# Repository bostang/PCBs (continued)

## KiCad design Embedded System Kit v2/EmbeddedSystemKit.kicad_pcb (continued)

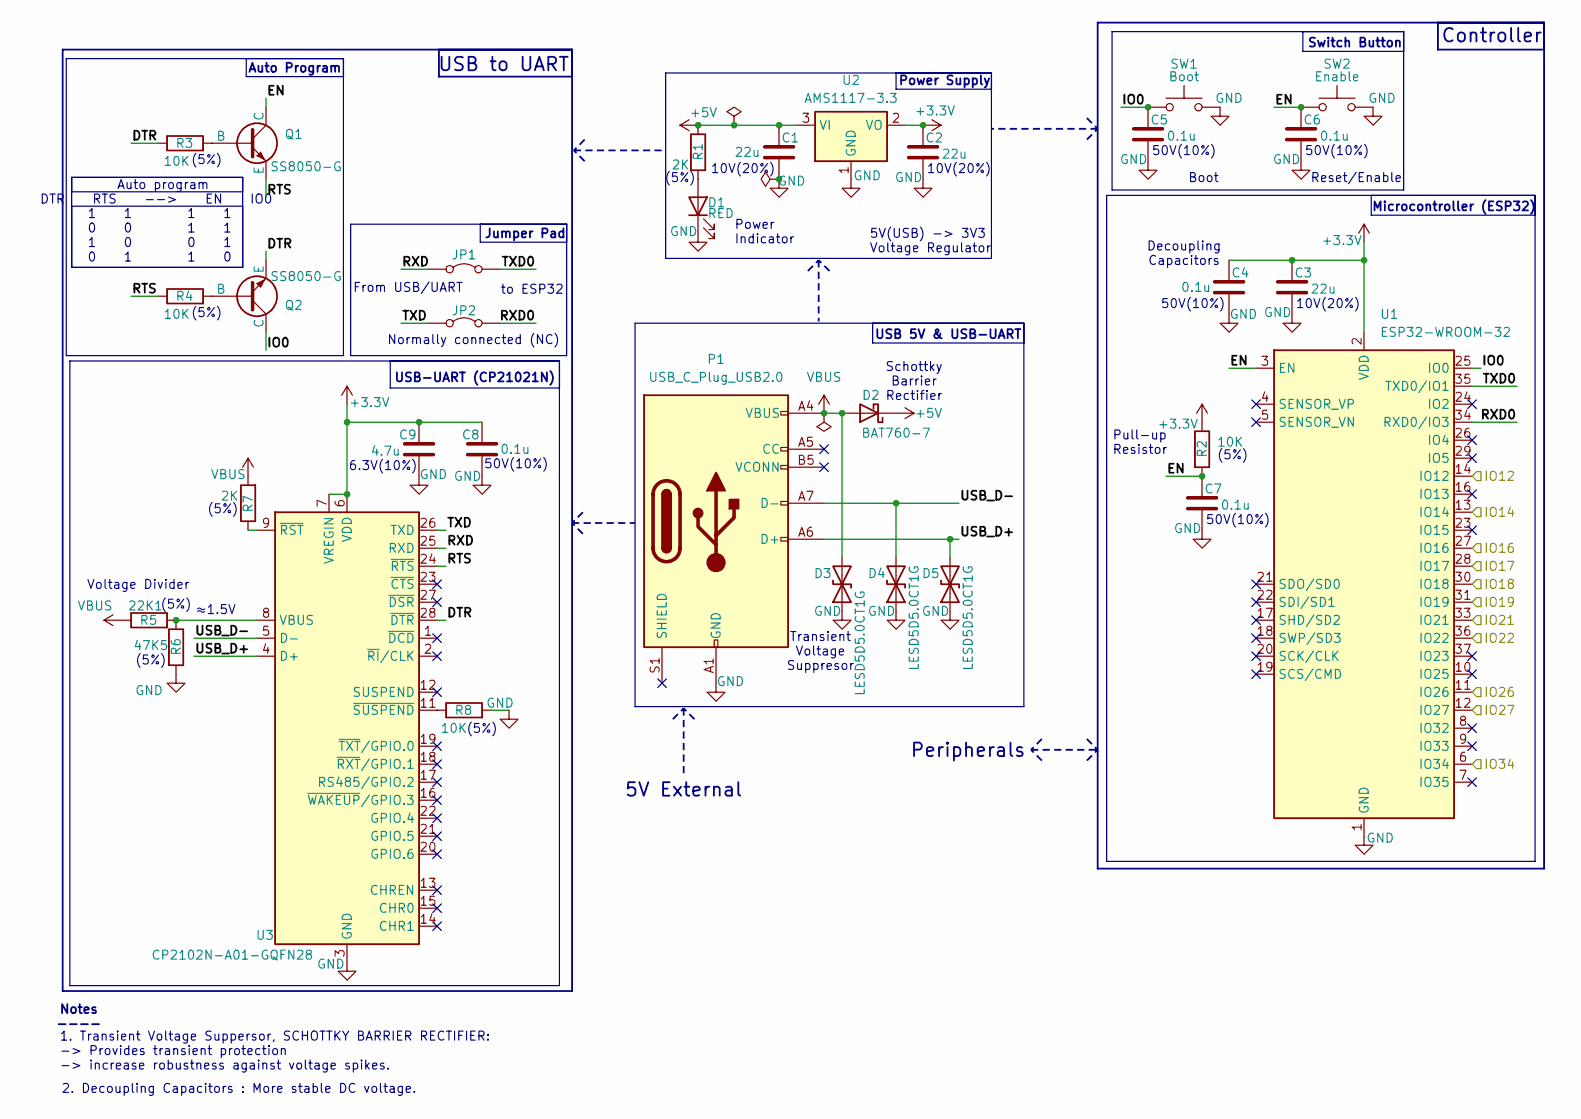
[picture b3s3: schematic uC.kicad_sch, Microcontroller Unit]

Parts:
C1, C2, C3: 22u; C_0805_2012Metric
C4, C5, C6, C7: 0.1u; C_0805_2012Metric
C8: 0.1u; C_0402_1005Metric
C9: 4.7u; C_0402_1005Metric
D1: RED; LED_0805_2012Metric
D2: BAT760-7; D_SOD-323
D3, D4, D5: LESD5D5.0CT1G; D_SOD-523
JP1, JP2: Jumper_2_Bridged; SolderJumper-2_P1.3mm_Bridged_RoundedPad1.0x1.5mm
P1: USB_C_Plug_USB2.0; USB_C_Receptacle_GCT_USB4105-xx-A_16P_TopMnt_Horizontal
Q1, Q2: SS8050-G; SOT-23
R1: 2K; R_0805_2012Metric
R2: 10K; R_0805_2012Metric
R3, R4, R8: 10K; R_0402_1005Metric
R5: 22K1; R_0402_1005Metric
R6: 47K5; R_0402_1005Metric
R7: 2K; R_0402_1005Metric
SW1: Boot; SW_SPST_B3U-1000P
SW2: Enable; SW_SPST_B3U-1000P
U1: ESP32-WROOM-32
U2: AMS1117-3.3; SOT-223-3_TabPin2
U3: CP2102N-A01-GQFN28; QFN-28-1EP_5x5mm_P0.5mm_EP3.35x3.35mm

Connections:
+3.3V: C2.1, C3.1, C4.1, C8.1, C9.1, R2.1, U1.2 (VDD), U2.2 (VO), U3.6 (VDD), U3.7 (VREGIN); also elsewhere on the board
+5V: C1.1, D2.1 (K), R1.1, U2.3 (VI); also elsewhere on the board
/LCD_SCL: U1.36 (IO22); also elsewhere on the board
/LCD_SDA: U1.33 (IO21); also elsewhere on the board
/LED1: U1.14 (IO12); also elsewhere on the board
/LED2: U1.13 (IO14); also elsewhere on the board
/LED3: U1.11 (IO26); also elsewhere on the board
/LED4: U1.12 (IO27); also elsewhere on the board
/PB1: U1.27 (IO16); also elsewhere on the board
/PB2: U1.28 (IO17); also elsewhere on the board
/PB3: U1.30 (IO18); also elsewhere on the board
/PB4: U1.31 (IO19); also elsewhere on the board
/POT: U1.6 (IO34); also elsewhere on the board
/uC/DTR: Q2.3 (E), R3.1, U3.28 (~DTR)
/uC/EN: C6.1, C7.1, Q1.1 (C), R2.2, SW2.1, U1.3 (EN)
/uC/IO0: C5.1, Q2.1 (C), SW1.1, U1.25 (IO0)
/uC/RTS: Q1.3 (E), R4.1, U3.24 (~RTS)
/uC/RXD: JP1.1 (A), U3.25 (RXD)
/uC/RXD0: JP2.2 (B), U1.34 (RXD0/IO3)
/uC/TXD: JP2.1 (A), U3.26 (TXD)
/uC/TXD0: JP1.2 (B), U1.35 (TXD0/IO1)
/uC/USB_D+: D5.2 (A2), P1.A6 (D+), U3.4 (D+)
/uC/USB_D-: D4.2 (A2), P1.A7 (D-), U3.5 (D-)
GND: C1.2, C2.2, C3.2, C4.2, C5.2, C6.2, C7.2, C8.2, C9.2, D1.1 (K), D3.1 (A1), D4.1 (A1), D5.1 (A1), P1.A1 (GND), P1.A12 (GND), P1.B1 (GND), P1.B12 (GND), R6.2, R8.2, SW1.2, SW2.2, U1.1 (GND), U1.15 (GND), U1.38 (GND), U1.39 (GND), U2.1 (GND), U3.3 (GND), U3.29 (GND); also elsewhere on the board
unnamed: D1.2 (A), R1.2
unnamed: Q1.2 (B), R3.2
unnamed: Q2.2 (B), R4.2
unnamed: R5.2, R6.1, U3.8 (VBUS)
unnamed: R7.1, U3.9 (~RST)
unnamed: R8.1, U3.11 (~SUSPEND)
VBUS: D2.2 (A), D3.2 (A2), P1.A4 (VBUS), P1.A9 (VBUS), P1.B4 (VBUS), P1.B9 (VBUS), R5.1, R7.2

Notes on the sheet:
Auto program DTR RTS --> EN IO0 1 1 1 1 0 0 1 1 1 0 0 1 0 1 1 0
Normally connected (NC)
Transient Voltage Suppresor
Auto Program
(5%)
10V(20%)
50V(10%)
Voltage Divider
Microcontroller (ESP32)
Pull-up Resistor
5V(USB) -> 3V3 Voltage Regulator
Power Indicator
From USB/UART
Schottky Barrier Rectifier
to ESP32
6.3V(10%)
Power Supply
Boot
5V External
Decoupling Capacitors
Peripherals
USB-UART (CP21021N)
Notes ----
Jumper Pad
≈1.5V
2. Decoupling Capacitors : More stable DC voltage.
Switch Button
Controller
1. Transient Voltage Suppersor, SCHOTTKY BARRIER RECTIFIER: -> Provides transient protection -> increase robustness against voltage spikes.
USB 5V & USB-UART
USB to UART
Reset/Enable

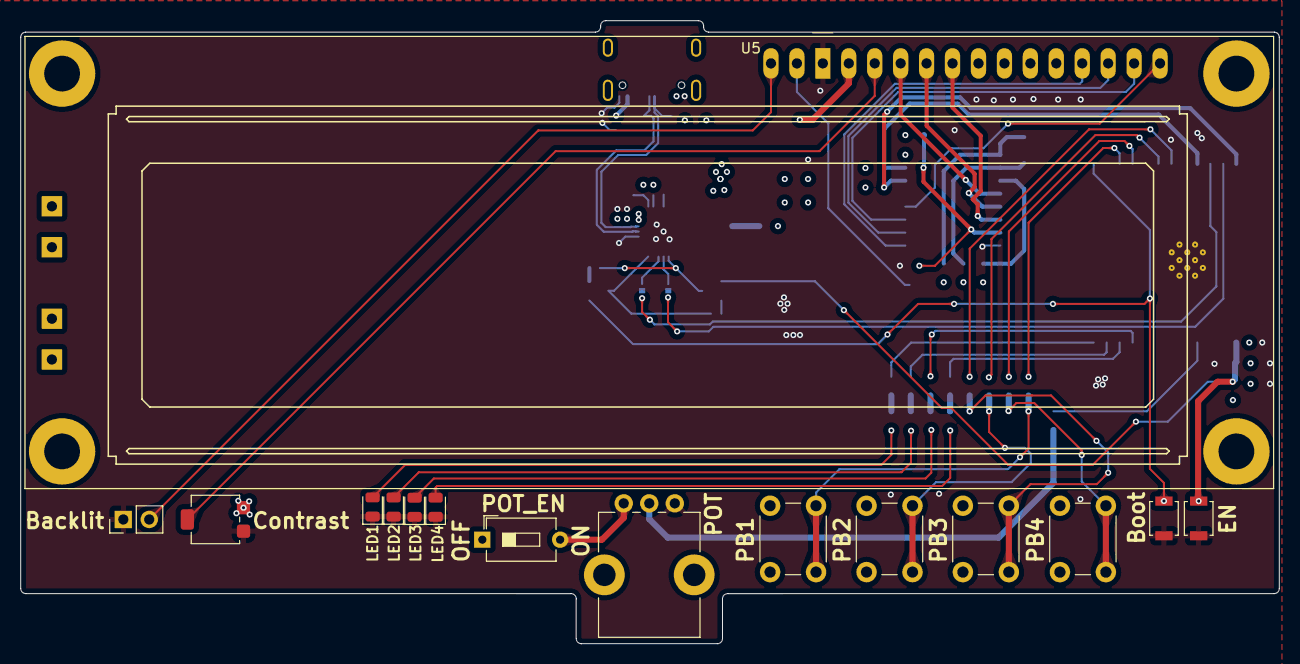
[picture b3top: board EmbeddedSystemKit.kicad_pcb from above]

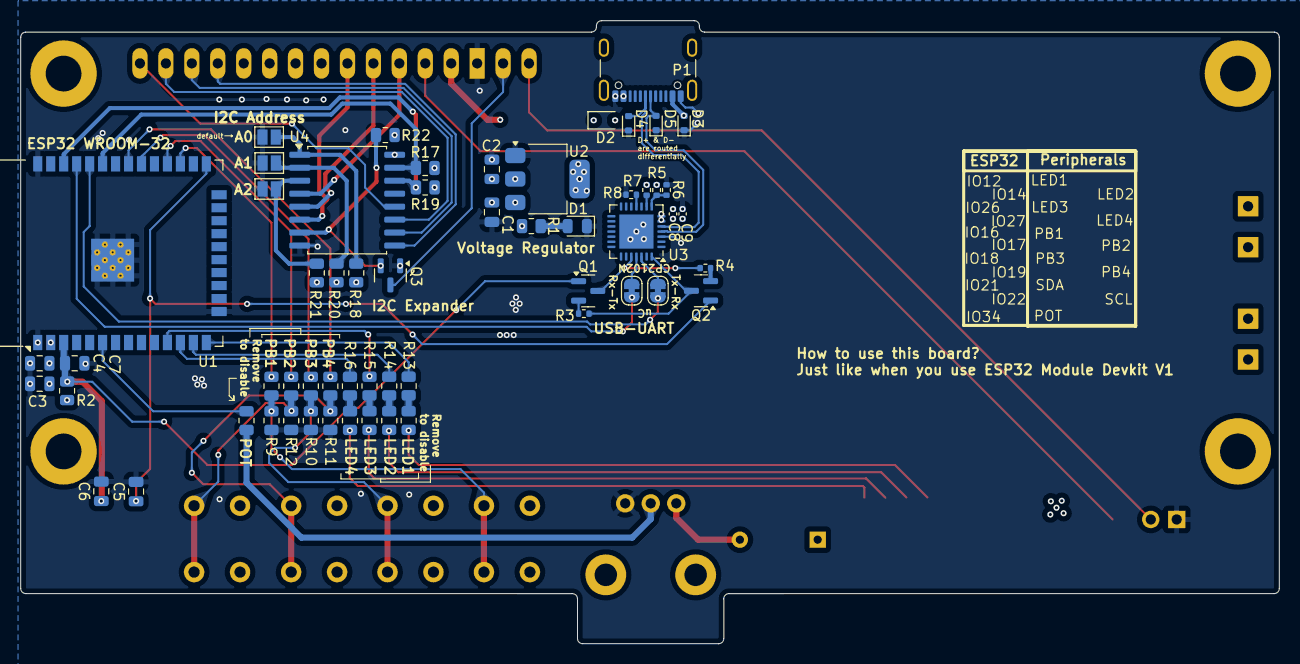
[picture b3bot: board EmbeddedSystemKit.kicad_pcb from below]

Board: 4 copper layers, 123.3 x 61.0 mm, 73 parts (58 on the bottom side), 59 nets.

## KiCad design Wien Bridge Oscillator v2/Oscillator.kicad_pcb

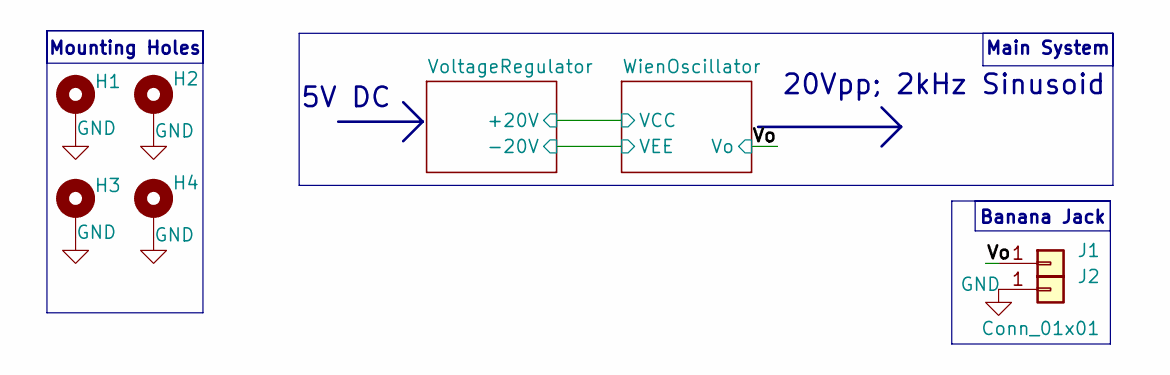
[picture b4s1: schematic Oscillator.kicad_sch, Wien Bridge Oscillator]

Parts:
H1, H2, H3, H4: MountingHole_Pad; MountingHole_2.2mm_M2_Pad_Via
J1, J2: Conn_01x01; TestPoint_Pad_4.0x4.0mm

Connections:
/Vo: J1.1; also elsewhere on the board
GND: H1.1, H2.1, H3.1, H4.1, J2.1; also elsewhere on the board

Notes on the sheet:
20Vpp; 2kHz Sinusoid
5V DC
Mounting Holes
Banana Jack
Main System

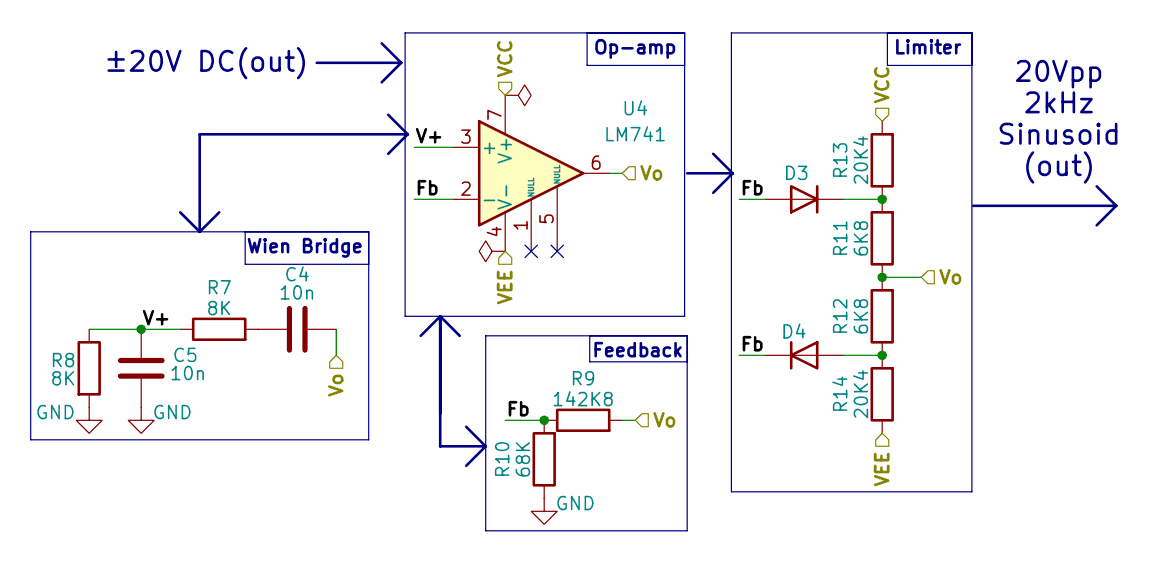
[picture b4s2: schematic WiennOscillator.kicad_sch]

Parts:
C4, C5: 10n; C_0805_2012Metric
D3, D4: D; D_SOD-323
R7, R8: 8K; R_0805_2012Metric
R9: 142K8; R_0805_2012Metric
R10: 68K; R_0805_2012Metric
R11, R12: 6K8; R_0805_2012Metric
R13, R14: 20K4; R_0805_2012Metric
U4: LM741; SOIC-8_3.9x4.9mm_P1.27mm

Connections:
/Vo: C4.2, R9.2, R11.1, R12.2, U4.6; also elsewhere on the board
/VoltageRegulator/+20V: R13.2, U4.7 (V+); also elsewhere on the board
/VoltageRegulator/-20V: R14.1, U4.4 (V-); also elsewhere on the board
/WienOscillator/Fb: D3.2 (A), D4.1 (K), R9.1, R10.2, U4.2 (-)
/WienOscillator/V+: C5.1, R7.1, R8.1, U4.3 (+)
GND: C5.2, R8.2, R10.1; also elsewhere on the board
unnamed: C4.1, R7.2
unnamed: D3.1 (K), R11.2, R13.1
unnamed: D4.2 (A), R12.1, R14.2

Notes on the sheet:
Feedback
Limiter
Wien Bridge
±20V DC(out)
20Vpp 2kHz Sinusoid (out)
Op-amp

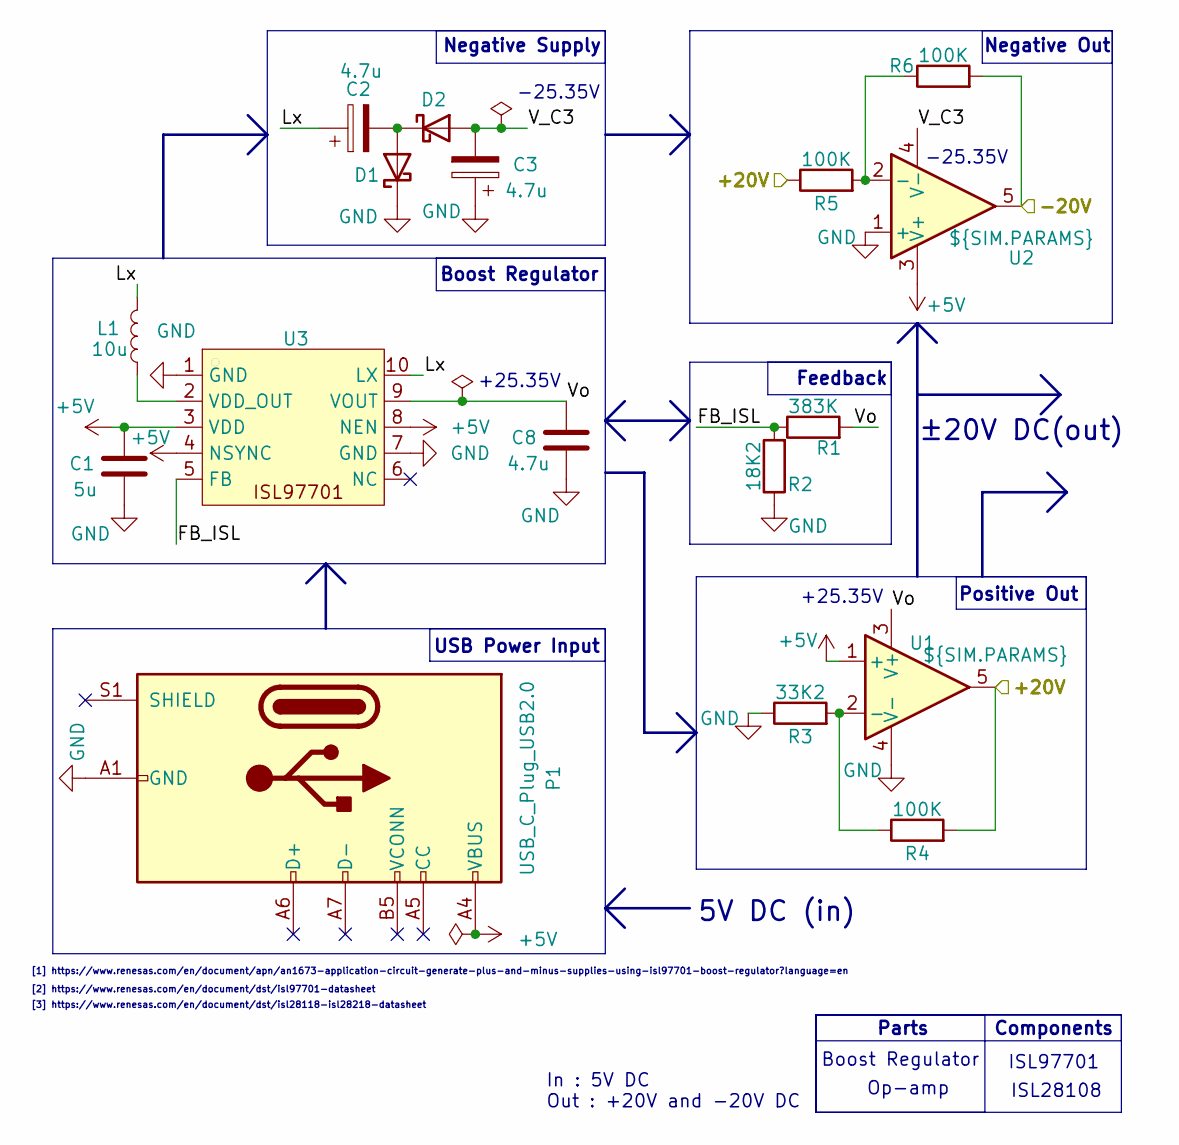
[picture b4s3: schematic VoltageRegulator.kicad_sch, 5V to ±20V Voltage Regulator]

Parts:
C1: 5u; C_0402_1005Metric
C2, C3: 4.7u; CP_Elec_3x5.3
C8: 4.7u; C_0402_1005Metric
D1, D2: D_Schottky; D_SOD-123
L1: 10u; L_KOHERelec_MDA5030
P1: USB_C_Plug_USB2.0; USB_C_Receptacle_GCT_USB4105-xx-A_16P_TopMnt_Horizontal
R1: 383K; R_0805_2012Metric
R2: 18K2; R_0805_2012Metric
R3: 33K2; R_0805_2012Metric
R4, R5, R6: 100K; R_0805_2012Metric
U1, U2: ${SIM.PARAMS}; SOIC-8_3.9x4.9mm_P1.27mm
U3: DFN-10-1EP_3x3mm_P0.5mm_EP1.65x2.38mm

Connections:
+5V: C1.1, P1.A4 (VBUS), P1.A9 (VBUS), P1.B4 (VBUS), P1.B9 (VBUS), U1.1 (+), U2.3 (V+), U3.3 (VDD), U3.4 (NSYNC), U3.8 (NEN)
/VoltageRegulator/+20V: R4.2, R5.1, U1.5; also elsewhere on the board
/VoltageRegulator/-20V: R6.2, U2.5; also elsewhere on the board
/VoltageRegulator/FB_ISL: R1.1, R2.2, U3.5 (FB)
/VoltageRegulator/Lx: C2.1, L1.2, U3.10 (LX)
/VoltageRegulator/V_C3: C3.2, D2.2 (A), U2.4 (V-)
/VoltageRegulator/Vo: C8.1, R1.2, U1.3 (V+), U3.9 (VOUT)
GND: C1.2, C3.1, C8.2, D1.1 (K), P1.A1 (GND), P1.A12 (GND), P1.B1 (GND), P1.B12 (GND), R2.1, R3.1, U1.4 (V-), U2.1 (+), U3.1 (GND), U3.7 (GND); also elsewhere on the board
unnamed: C2.2, D1.2 (A), D2.1 (K)
unnamed: R3.2, R4.1, U1.2 (-)
unnamed: R5.2, R6.1, U2.2 (-)
unnamed: L1.1, U3.2 (VDD_OUT)

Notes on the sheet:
In : 5V DC Out : +20V and -20V DC
Positive Out
Feedback
[1] https://www.renesas.com/en/document/apn/an1673-application-circuit-generate-plus-and-minus-supplies-using-isl97701-boost-regulator?language=en
ISL28108
Negative Out
-25.35V
5V DC (in)
Components
ISL97701
+25.35V
Boost Regulator
±20V DC(out)
USB Power Input
[2] https://www.renesas.com/en/document/dst/isl97701-datasheet
Negative Supply
Parts
[3] https://www.renesas.com/en/document/dst/isl28118-isl28218-datasheet
Op-amp

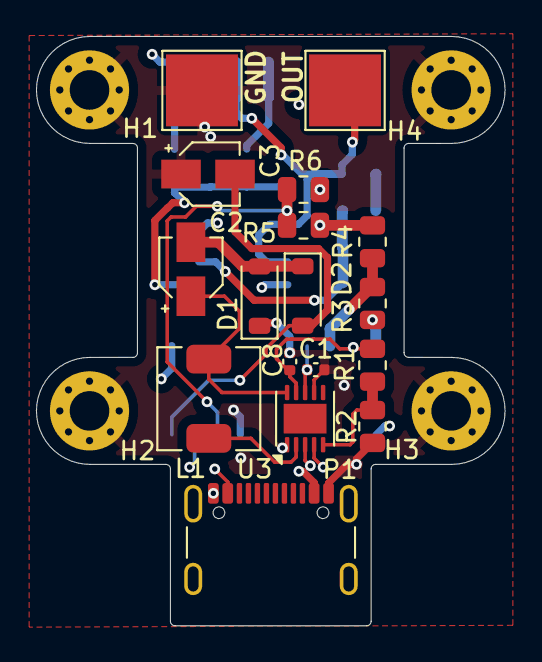
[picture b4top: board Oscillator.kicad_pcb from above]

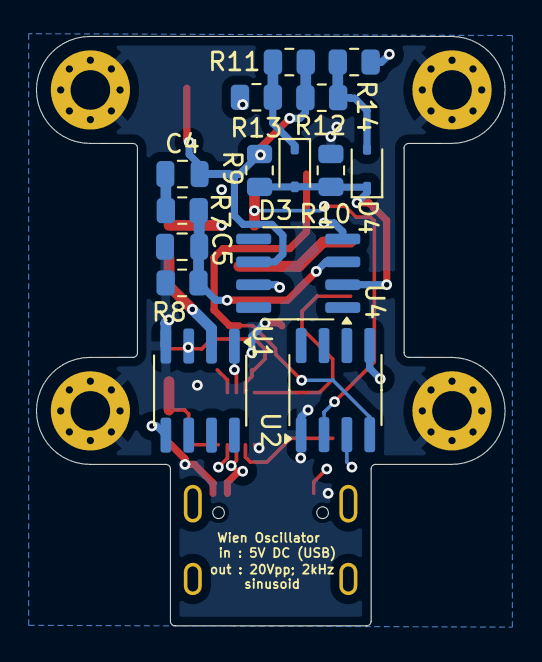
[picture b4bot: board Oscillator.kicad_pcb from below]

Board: 4 copper layers, 26.0 x 32.7 mm, 36 parts (15 on the bottom side), 18 nets.

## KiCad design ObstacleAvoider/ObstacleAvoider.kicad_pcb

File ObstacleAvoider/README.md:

# Obstacle Avoider

# Skematik

# Tampilan

## Tampak Atas

## Tampak Bawah

## Bird-view

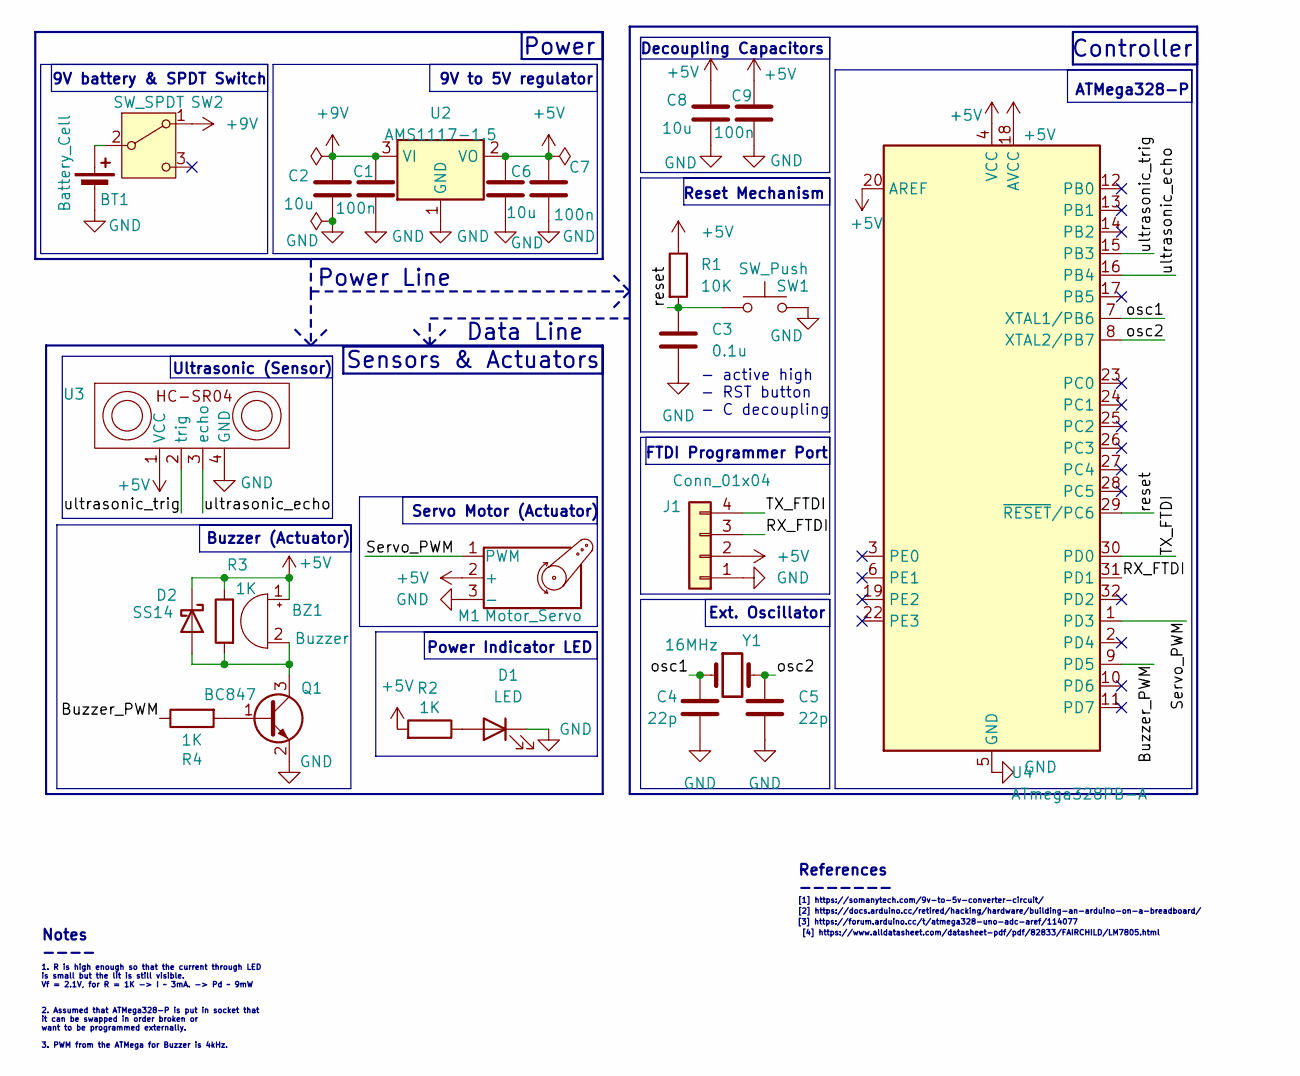
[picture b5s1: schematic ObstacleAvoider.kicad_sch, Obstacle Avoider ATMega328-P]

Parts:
BT1: Battery_Cell; BatteryHolder_Eagle_12BH611-GR
BZ1: Buzzer; MagneticBuzzer_Kobitone_254-EMB84Q-RO
C1, C7, C9: 100n; C_0805_2012Metric
C2, C6, C8: 10u; C_0805_2012Metric
C3: 0.1u; C_0805_2012Metric
C4, C5: 22p; C_0805_2012Metric
D1: LED; LED_0805_2012Metric
D2: SS14; D_SMA
J1: Conn_01x04; PinHeader_1x04_P2.54mm_Vertical_SMD_Pin1Left
M1: Motor_Servo; PinHeader_1x03_P2.54mm_Vertical_SMD_Pin1Left
Q1: BC847; SOT-23
R1: 10K; R_0805_2012Metric
R2, R3, R4: 1K; R_0805_2012Metric
SW1: SW_Push; SW_SPST_B3U-1000P
SW2: SW_SPDT; SW_SPDT_PCM12
U2: AMS1117-1.5; SOT-223-3_TabPin2
U3: PinHeader_1x04_P2.54mm_Vertical_SMD_Pin1Left
U4: ATmega328PB-A; TQFP-32_7x7mm_P0.8mm
Y1: 16MHz; Crystal_SMD_5032-2Pin_5.0x3.2mm

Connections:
+5V: BZ1.1 (+), C6.1, C7.1, C8.1, C9.1, D2.1 (K), J1.2, M1.2 (+), R1.1, R2.2, R3.1, U2.2 (VO), U3.1 (VCC), U4.4 (VCC), U4.18 (AVCC), U4.20 (AREF)
+9V: C1.1, C2.1, SW2.1 (A), U2.3 (VI)
/Buzzer_PWM: R4.1, U4.9 (PD5)
/RX_FTDI: J1.3, U4.31 (PD1)
/Servo_PWM: M1.1 (PWM), U4.1 (PD3)
/TX_FTDI: J1.4, U4.30 (PD0)
/osc1: C4.1, U4.7 (XTAL1/PB6), Y1.1
/osc2: C5.1, U4.8 (XTAL2/PB7), Y1.2
/reset: C3.1, R1.2, SW1.1, U4.29 (~RESET/PC6)
/ultrasonic_echo: U3.3 (echo), U4.16 (PB4)
/ultrasonic_trig: U3.2 (trig), U4.15 (PB3)
GND: BT1.2 (-), C1.2, C2.2, C3.2, C4.2, C5.2, C6.2, C7.2, C8.2, C9.2, D1.1 (K), J1.1, M1.3 (-), Q1.2 (E), SW1.2, U2.1 (GND), U3.4 (GND), U4.5 (GND), U4.21 (GND)
unnamed: BT1.1 (+), SW2.2 (B)
unnamed: BZ1.2 (-), D2.2 (A), Q1.3 (C), R3.2
unnamed: D1.2 (A), R2.1
unnamed: Q1.1 (B), R4.2

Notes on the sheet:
Ext. Oscillator
FTDI Programmer Port
Reset Mechanism
Decoupling Capacitors
Power Indicator LED
Ultrasonic (Sensor)
Notes ----
Data Line
Sensors & Actuators
2. Assumed that ATMega328-P is put in socket that it can be swapped in order broken or want to be programmed externally.
Controller
Power
9V battery & SPDT Switch
1. R is high enough so that the current through LED is small but the lit is still visible. Vf = 2.1V, for R = 1K -> I ~ 3mA. -> Pd ~ 9mW
References -------
- active high - RST button - C decoupling
[4] https://www.alldatasheet.com/datasheet-pdf/pdf/82833/FAIRCHILD/LM7805.html
[2] https://docs.arduino.cc/retired/hacking/hardware/building-an-arduino-on-a-breadboard/
[3] https://forum.arduino.cc/t/atmega328-uno-adc-aref/114077
Servo Motor (Actuator)
9V to 5V regulator
[1] https://somanytech.com/9v-to-5v-converter-circuit/
Power Line
Buzzer (Actuator)
3. PWM from the ATMega for Buzzer is 4kHz.
ATMega328-P

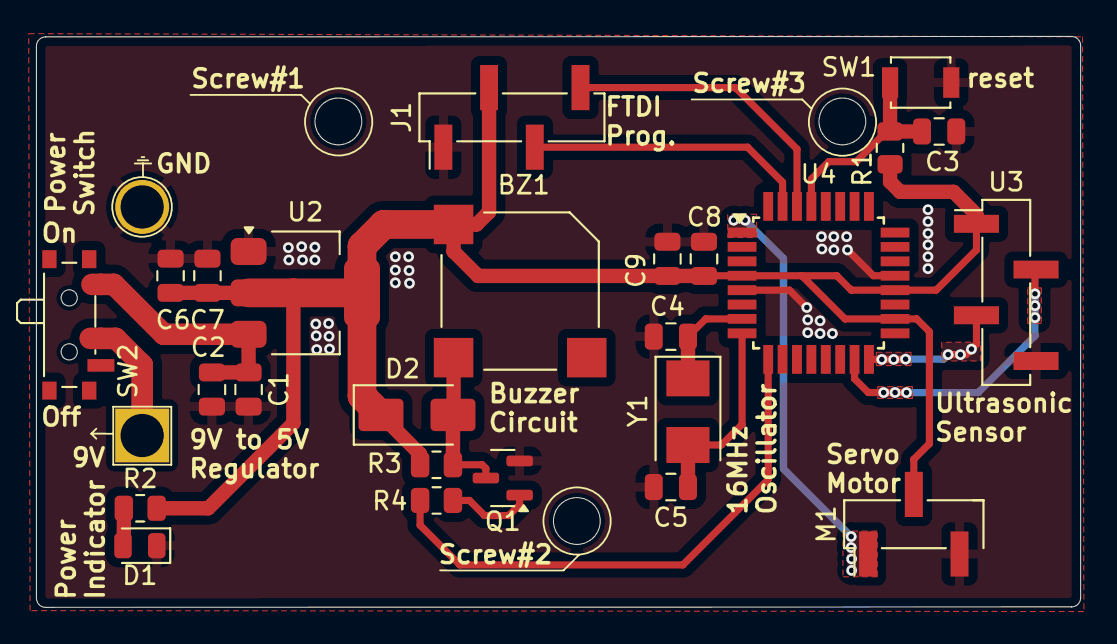
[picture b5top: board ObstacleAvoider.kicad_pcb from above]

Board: 2 copper layers, 58.0 x 31.7 mm, 26 parts (1 on the bottom side), 16 nets.

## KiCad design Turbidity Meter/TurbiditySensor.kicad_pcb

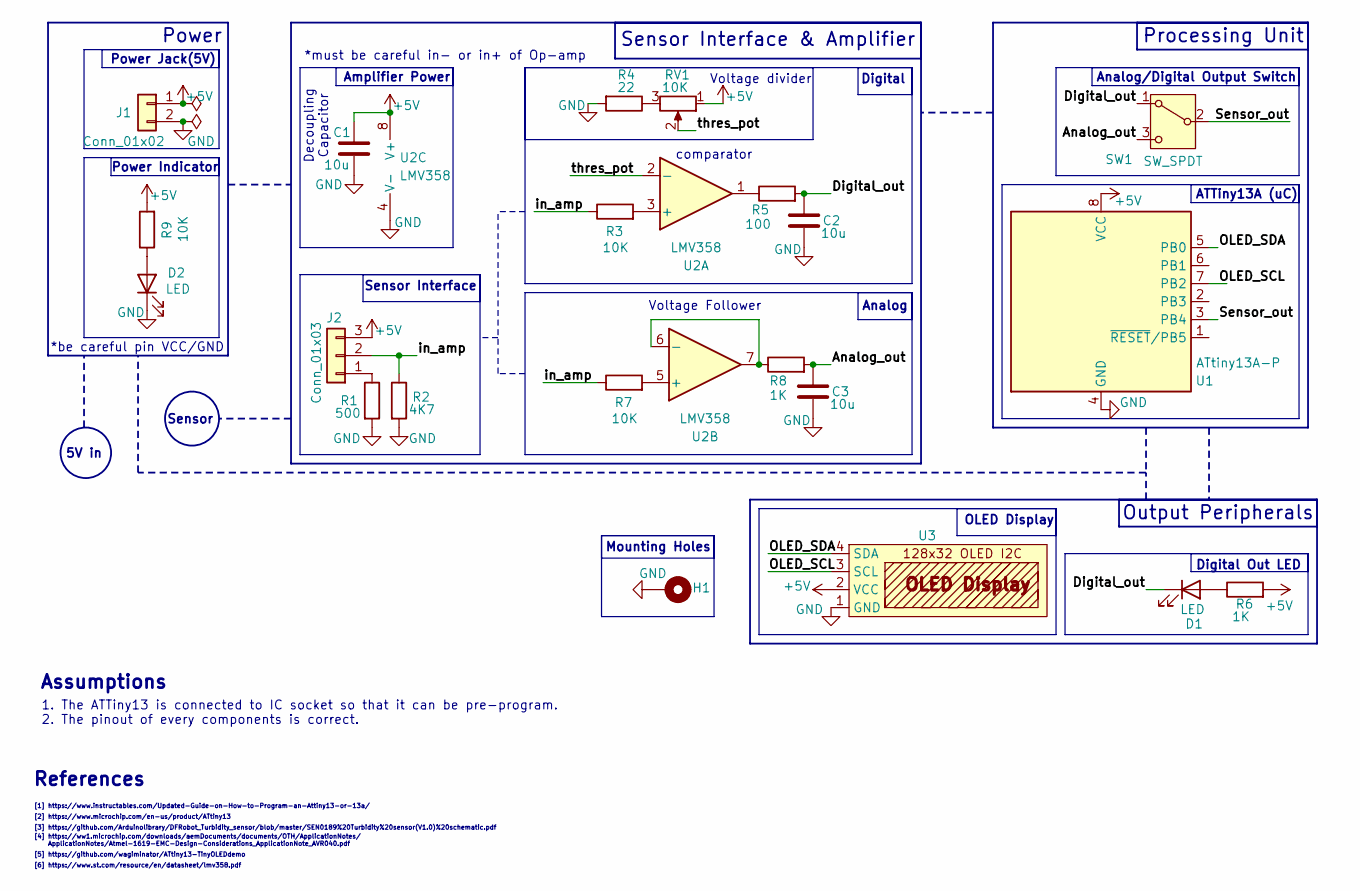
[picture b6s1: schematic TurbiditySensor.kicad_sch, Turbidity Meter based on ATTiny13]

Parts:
C1, C2, C3: 10u; C_0805_2012Metric
D1, D2: LED; LED_0805_2012Metric
H1: MountingHole_Pad; MountingHole_2.2mm_M2_Pad_Via
J1: Conn_01x02; BarrelJack_CUI_PJ-063AH_Horizontal
J2: Conn_01x03; JST_XH_S3B-XH-A-1_1x03_P2.50mm_Horizontal
R1: 500; R_0805_2012Metric
R2: 4K7; R_0805_2012Metric
R3, R7, R9: 10K; R_0805_2012Metric
R4: 22; R_0805_2012Metric
R5: 100; R_0805_2012Metric
R6, R8: 1K; R_0805_2012Metric
RV1: 10K; Potentiometer_Bourns_3266P_Horizontal
SW1: SW_SPDT; SW_Slide_SPDT_Angled_CK_OS102011MA1Q
U1: ATtiny13A-P; DIP-8_W7.62mm
U2: LMV358; SOIC-8_3.9x4.9mm_P1.27mm
U3: oled128x32

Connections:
+5V: C1.2, J1.1, J2.3, R6.2, R9.2, RV1.1, U1.8 (VCC), U2.8 (V+), U3.2 (VCC)
/Analog_out: C3.2, R8.2, SW1.3 (C)
/Digital_out: C2.2, D1.1 (K), R5.2, SW1.1 (A)
/OLED_SCL: U1.7 (PB2), U3.3 (SCL)
/OLED_SDA: U1.5 (PB0), U3.4 (SDA)
/Sensor_out: SW1.2 (B), U1.3 (PB4)
/in_amp: J2.2, R2.1, R3.1, R7.1
/thres_pot: RV1.2, U2.2 (-)
GND: C1.1, C2.1, C3.1, D2.1 (K), H1.1, J1.2, R1.2, R2.2, R4.2, U1.4 (GND), U2.4 (V-), U3.1 (GND)
unnamed: D1.2 (A), R6.1
unnamed: D2.2 (A), R9.1
unnamed: J2.1, R1.1
unnamed: R4.1, RV1.3
unnamed: R5.1, U2.1
unnamed: R3.2, U2.3 (+)
unnamed: R7.2, U2.5 (+)
unnamed: R8.1, U2.6 (-), U2.7

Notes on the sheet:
comparator
Decoupling Capacitor
OLED Display
Power Indicator
Mounting Holes
[6] https://www.st.com/resource/en/datasheet/lmv358.pdf
Power Jack(5V)
Sensor Interface & Amplifier
*be careful pin VCC/GND
Sensor
Assumptions
Analog
Output Peripherals
References
[3] https://github.com/Arduinolibrary/DFRobot_Turbidity_sensor/blob/master/SEN0189%20Turbidity%20sensor(V1.0)%20schematic.pdf
Voltage divider
[5] https://github.com/wagiminator/ATtiny13-TinyOLEDdemo
[1] https://www.instructables.com/Updated-Guide-on-How-to-Program-an-Attiny13-or-13a/
Voltage Follower
[4] https://ww1.microchip.com/downloads/aemDocuments/documents/OTH/ApplicationNotes/ ApplicationNotes/Atmel-1619-EMC-Design-Considerations_ApplicationNote_AVR040.pdf
Digital
Analog/Digital Output Switch
Sensor Interface
Digital Out LED
*must be careful in- or in+ of Op-amp
1. The ATTiny13 is connected to IC socket so that it can be pre-program. 2. The pinout of every components is correct.
Amplifier Power
[2] https://www.microchip.com/en-us/product/ATtiny13
5V in
ATTiny13A (uC)
Processing Unit
Power

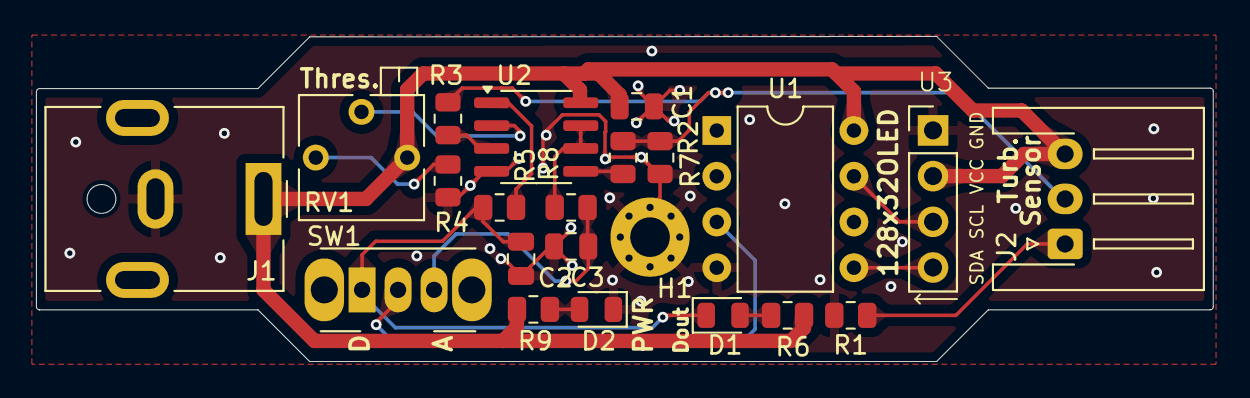
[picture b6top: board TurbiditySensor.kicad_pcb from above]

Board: 2 copper layers, 65.4 x 18.1 mm, 22 parts (0 on the bottom side), 17 nets.

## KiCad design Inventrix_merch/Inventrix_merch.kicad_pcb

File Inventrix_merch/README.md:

# Inventrix KeyChain

Sebuah gantungan kunci PCB bertemakan elektronika (IC) dengan logo Inventrix dan ITB (flipped) untuk merchandise booth Inventrix pada acara EE-days 2024.

# Skematik (*dummy*)

# Tampilan

## Tampak Atas

## Tampak Bawah

## Bird-view

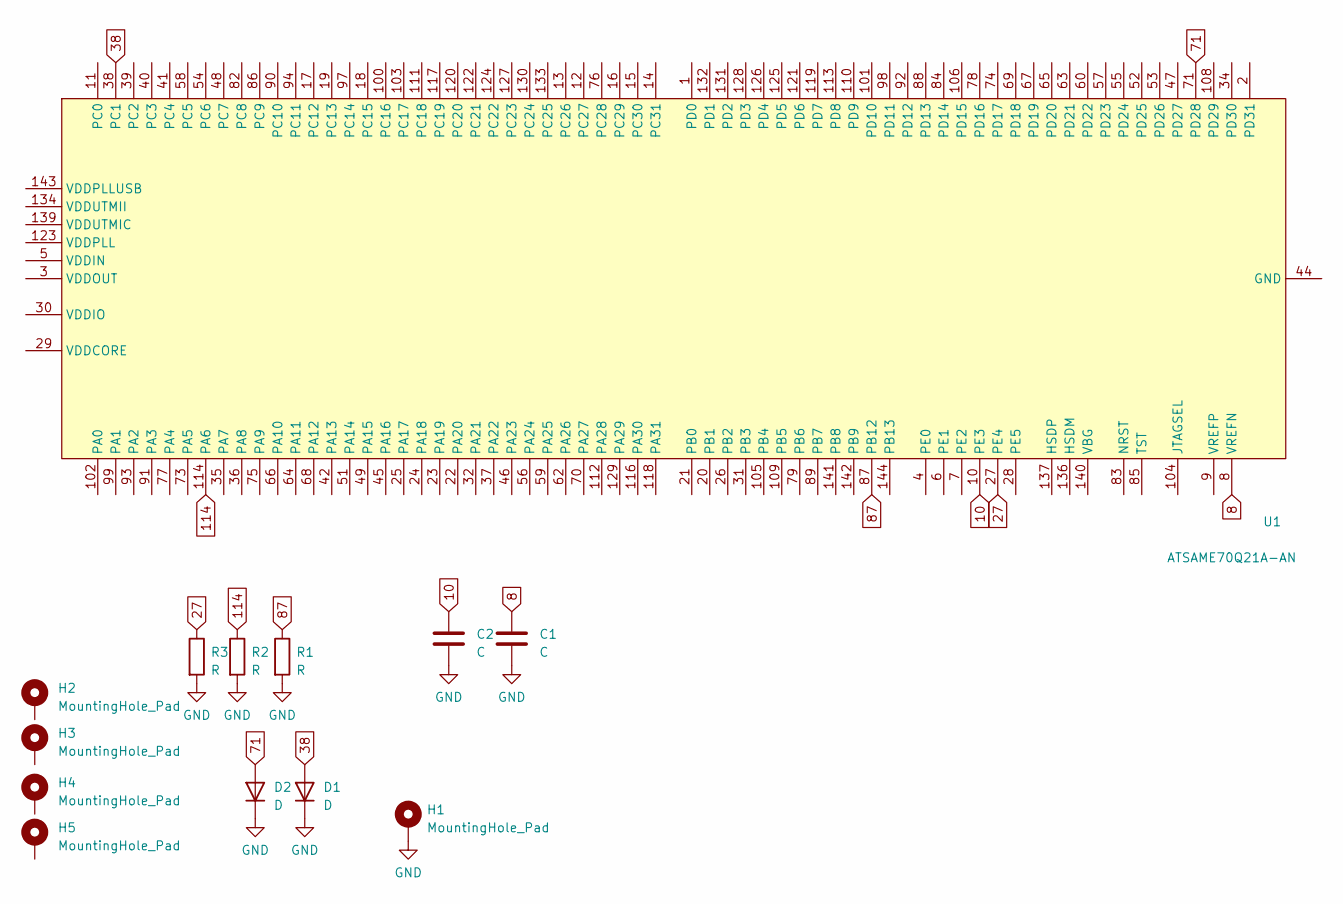
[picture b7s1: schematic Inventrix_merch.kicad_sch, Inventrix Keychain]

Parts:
C1, C2: C; C_0402_1005Metric
D1, D2: D; D_0402_1005Metric
H1: MountingHole_Pad; MountingHole_2.7mm_Pad_Via
H2, H3, H4, H5: MountingHole_Pad; MountingHole_2.2mm_M2_DIN965_Pad
R1, R2, R3: R; R_0402_1005Metric
U1: ATSAME70Q21A-AN; LQFP-144_20x20mm_P0.5mm

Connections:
8: C1.1, U1.8 (VREFN)
10: C2.1, U1.10 (PE3)
27: R3.1, U1.27 (PE4)
38: D1.2 (A), U1.38 (PC1)
71: D2.2 (A), U1.71 (PD28)
87: R1.1, U1.87 (PB12)
114: R2.1, U1.114 (PA6)
GND: C1.2, C2.2, D1.1 (K), D2.1 (K), H1.1, R1.2, R2.2, R3.2
unnamed: U1.44 (GND), U1.61 (GND), U1.95 (GND), U1.115 (GND), U1.135 (GND), U1.138 (GND)
unnamed: U1.29 (VDDCORE), U1.33 (VDDCORE), U1.50 (VDDCORE), U1.81 (VDDCORE), U1.107 (VDDCORE)
unnamed: U1.30 (VDDIO), U1.43 (VDDIO), U1.72 (VDDIO), U1.80 (VDDIO), U1.96 (VDDIO)

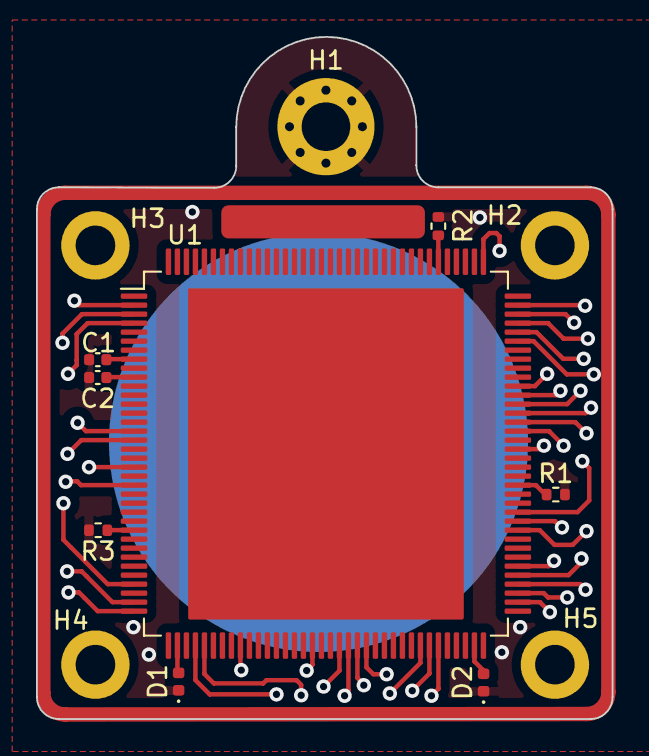
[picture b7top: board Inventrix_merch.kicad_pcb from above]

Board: 2 copper layers, 32.0 x 37.9 mm, 13 parts (0 on the bottom side), 11 nets.

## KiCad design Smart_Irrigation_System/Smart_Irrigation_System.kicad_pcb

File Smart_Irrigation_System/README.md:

# Smart Irrigation System

PCB Tugas Akhir Jefferson Grizzlie tentang smart irrigation system (membantu kawan).

# Skematik

# Tampilan

## Tampak Atas

## Tampak Bawah

## Bird-view

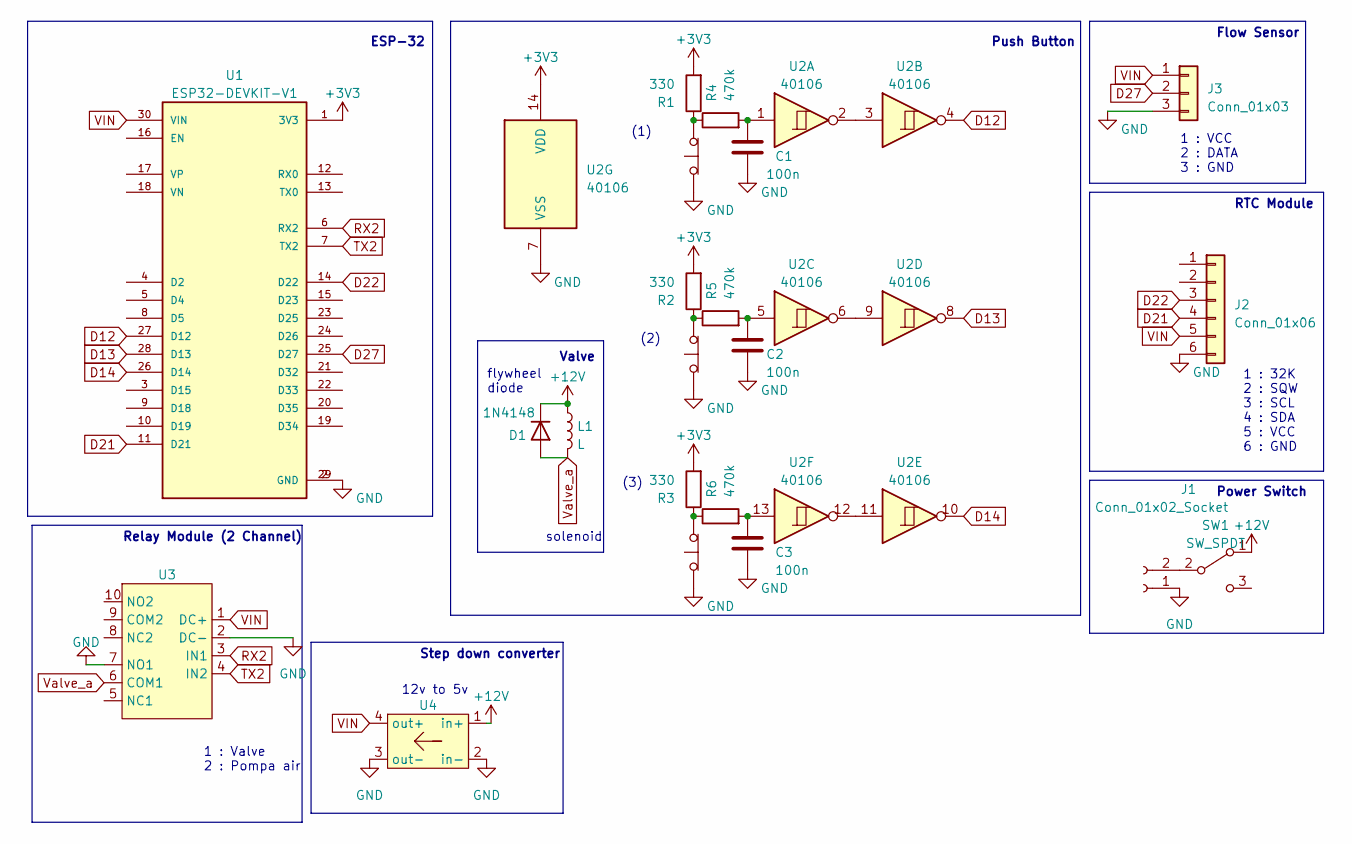
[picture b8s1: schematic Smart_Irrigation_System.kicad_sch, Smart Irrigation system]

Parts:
C1, C2, C3: 100n; C_0805_2012Metric
D1: 1N4148; D_5KP_P10.16mm_Horizontal
J1: Conn_01x02_Socket; JST_EH_B2B-EH-A_1x02_P2.50mm_Vertical
J2: Conn_01x06; PinSocket_1x06_P2.54mm_Horizontal
J3: Conn_01x03; JST_EH_S3B-EH_1x03_P2.50mm_Horizontal
L1: L; TerminalBlock_Phoenix_MKDS-1,5-2-5.08_1x02_P5.08mm_Horizont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
R1, R2, R3: 330; R_0805_2012Metric
R4, R5, R6: 470k; R_0805_2012Metric
SW1: SW_SPDT; SW_E-Switch_EG1224_SPDT_Angled
SW2, SW3, SW4: SW_Push_Open; SW_PUSH-12mm
U1: ESP32-DEVKIT-V1; MODULE_ESP32_DEVKIT_V1; PARTREV N/A
U2: 40106; SOIC-14_3.9x8.7mm_P1.27mm
U3: Relay_2_Channel
U4: LM2596

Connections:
+3V3: R1.2, R2.2, R3.2, U1.1 (3V3), U2.14 (VDD)
+12V: D1.1 (K), L1.1, SW1.1 (A), U4.1 (in+)
D12: U1.27 (D12), U2.4
D13: U1.28 (D13), U2.8
D14: U1.26 (D14), U2.10
D21: J2.4, U1.11 (D21)
D22: J2.3, U1.14 (D22)
D27: J3.2, U1.25 (D27)
GND: C1.2, C2.2, C3.2, J1.1, J2.6, J3.3, SW2.1 (A), SW3.1 (A), SW4.1 (A), U1.2 (GND), U1.29 (GND), U2.7 (VSS), U3.2 (DC-), U3.7 (NO1), U4.2 (in-), U4.3 (out-)
unnamed: C1.1, R4.2, U2.1
unnamed: C2.1, R5.2, U2.5
unnamed: C3.1, R6.2, U2.13
unnamed: J1.2, SW1.2 (B)
unnamed: R1.1, R4.1, SW2.2 (B)
unnamed: R2.1, R5.1, SW3.2 (B)
unnamed: R3.1, R6.1, SW4.2 (B)
unnamed: U2.2, U2.3
unnamed: U2.6, U2.9
unnamed: U2.11, U2.12
RX2: U1.6 (RX2), U3.3 (IN1)
TX2: U1.7 (TX2), U3.4 (IN2)
VIN: J2.5, J3.1, U1.30 (VIN), U3.1 (DC+), U4.4 (out+)
Valve_a: D1.2 (A), L1.2, U3.6 (COM1)

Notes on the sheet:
Valve
(2)
ESP-32
(1)
1 : Valve 2 : Pompa air
Power Switch
flywheel diode
solenoid
Relay Module (2 Channel)
Push Button
Flow Sensor
1 : VCC 2 : DATA 3 : GND
1 : 32K 2 : SQW 3 : SCL 4 : SDA 5 : VCC 6 : GND
(3)
RTC Module
12v to 5v
Step down converter

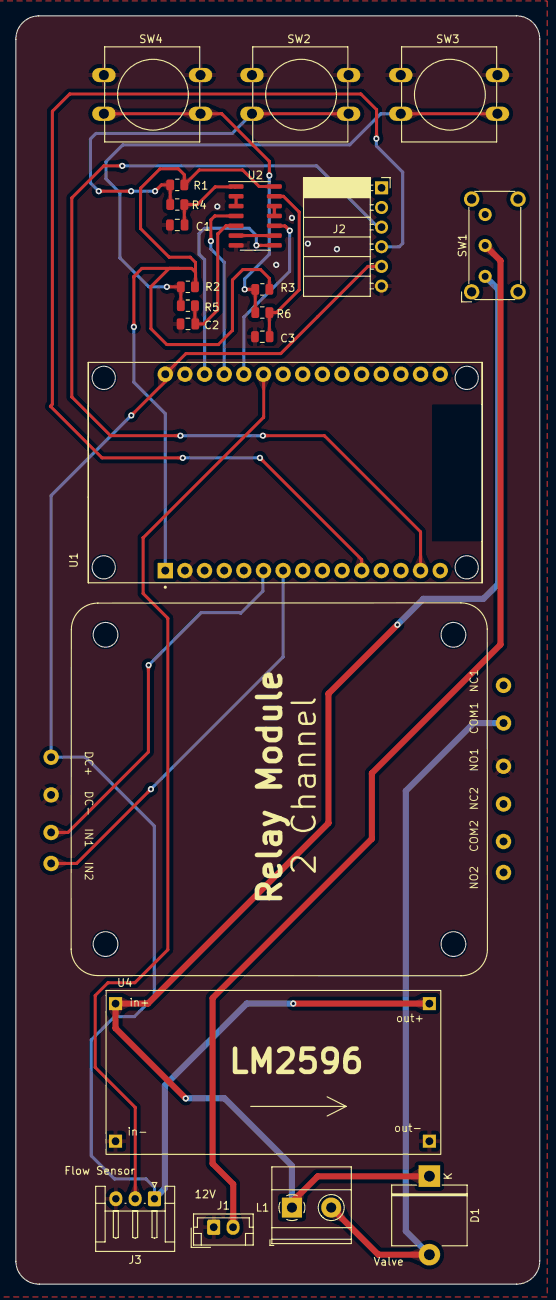
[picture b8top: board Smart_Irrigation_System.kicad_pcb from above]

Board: 2 copper layers, 67.8 x 164.1 mm, 22 parts (0 on the bottom side), 23 nets.

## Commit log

2024-04-20 +WMS
2024-04-20 Create README.md for WMS
2024-04-20 Update README.md WMS
2024-04-20 +gambar skematik WMS
2024-04-20 +RF Transceiver
2024-04-20 Update README.md RFTransceiver
2024-04-20 +Audiojack Banana Converter
2024-04-20 +Electronic Badge
2024-04-20 +SpyCam
2024-04-20 +Transistor Amplifier
2024-04-20 Wien Bridge Oscillator
2024-04-20 +Embedded System Kit
2024-04-20 +Keychain EL'20
2024-04-20 +Op Amp Circuits
2024-05-07 +WMS_v4
    menggunakan empat layer
2024-05-07 +gambar PCB v4
2024-05-07 + perbaikan PCB v4
2024-05-07 +file skematik, pcb, placement WMS_v4
2024-05-09 +gerber WMS v4.1
2024-05-12 + proyek ROV
    membantu Yolivia Robong Langi
2024-05-12 +Proyek Robot Evakuasi Gempa & Smart Irrigation System
    Membantu tugas akhir kawan dalam membuat PCB
2024-06-14 +final sourcecode and PCB
2024-06-19 +Inventrix keychain
2024-06-19 Update and rename README.md.txt to README.md (Inventrix merch)
2024-06-19 +zip complete project Inventrix Merch
2024-11-11 +PCB version 2
    - menggunakan 1 mikrokontroller
    - menggunakan modul LoRa untuk komunikasi
    - terdapat regulator tegangan 12V -> 3.3V
2024-11-11 +foto PCB v2
2024-11-11 +image skematik RF v2
2024-12-04 +Turbidity Meter (EL3013)
2024-12-04 Update README.md (.png -> .jpg)
2024-12-04 +gambar case
2024-12-05 + Obstacle avoider
    kerja praktik
2024-12-06 +Wien Bridge Oscillator v2
2024-12-07 +Embedded System Kit (v2)
2024-12-09 +PCB Jam Digital
2024-12-10 +Rangkaian Kit Op-Amp rangkaian v2
2024-12-10 Re-add Digital Clock
    because previously uploaded version has little bug : no buzzer.
